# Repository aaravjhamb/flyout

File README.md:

# flyout

a pcb hackercard that also functions as a drone ;D

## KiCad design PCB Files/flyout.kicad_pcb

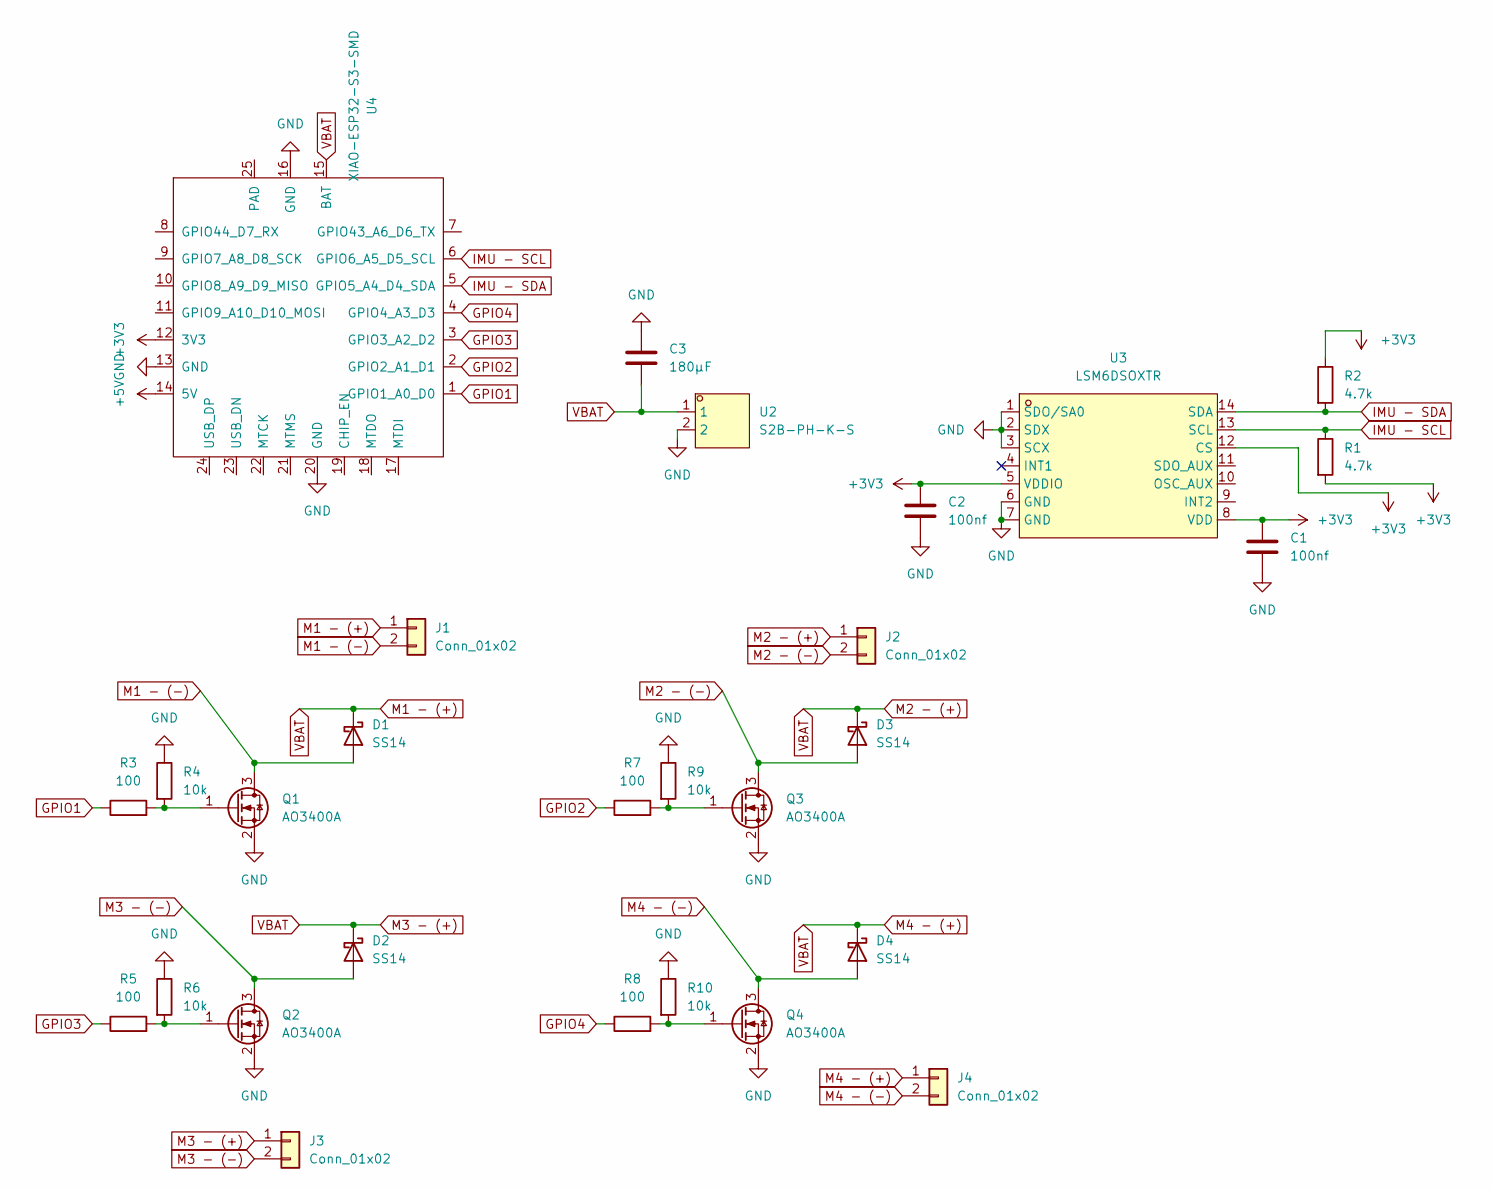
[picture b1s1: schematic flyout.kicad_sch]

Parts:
C1, C2: 100nf; C_0402_1005Metric
C3: 180µF; C_0402_1005Metric
D1, D2, D3, D4: SS14; D_SMA
J1, J2, J3, J4: Conn_01x02; SolderPad_1x02_SMD_1.5x2mm_P2.5mm
Q1, Q2, Q3, Q4: AO3400A; SOT-23
R1, R2: 4.7k; R_0402_1005Metric
R3, R5, R7, R8: 100; R_0402_1005Metric
R4, R6, R9, R10: 10k; R_0402_1005Metric
U2: S2B-PH-K-S; CONN-TH_S2B-PH-K-S-LF-SN; MPN S2B-PH-K-S(LF)(SN); LCSC Part C173752
U3: LSM6DSOXTR; LGA-14L_L3.0-W2.5-P0.50-TL; MPN LSM6DSOXTR; LCSC Part C481766
U4: XIAO-ESP32-S3-SMD

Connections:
+3V3: C1.1, C2.1, R1.2, R2.1, U3.5 (VDDIO), U3.8 (VDD), U3.12 (CS), U4.12 (3V3)
+5V: U4.14 (5V)
GND: C1.2, C2.2, C3.1, Q1.2 (S), Q2.2 (S), Q3.2 (S), Q4.2 (S), R4.1, R6.1, R9.1, R10.1, U2.2, U3.1 (SDO/SA0), U3.2 (SDX), U3.3 (SCX), U3.6 (GND), U3.7 (GND), U4.13 (GND), U4.16 (GND), U4.20 (GND)
GPIO1: R3.1, U4.1 (GPIO1_A0_D0)
GPIO2: R7.1, U4.2 (GPIO2_A1_D1)
GPIO3: R5.1, U4.3 (GPIO3_A2_D2)
GPIO4: R8.1, U4.4 (GPIO4_A3_D3)
IMU - SCL: R1.1, U3.13 (SCL), U4.6 (GPIO6_A5_D5_SCL)
IMU - SDA: R2.2, U3.14 (SDA), U4.5 (GPIO5_A4_D4_SDA)
M1 - (+): C3.2, D1.1 (K), D2.1 (K), D3.1 (K), D4.1 (K), J1.1, J2.1, J3.1, J4.1, U2.1, U4.15 (BAT)
M1 - (-): D1.2 (A), J1.2, Q1.3 (D)
M2 - (-): D3.2 (A), J2.2, Q3.3 (D)
M3 - (-): D2.2 (A), J3.2, Q2.3 (D)
M4 - (-): D4.2 (A), J4.2, Q4.3 (D)
unnamed: Q1.1 (G), R3.2, R4.2
unnamed: Q2.1 (G), R5.2, R6.2
unnamed: Q3.1 (G), R7.2, R9.2
unnamed: Q4.1 (G), R8.2, R10.2

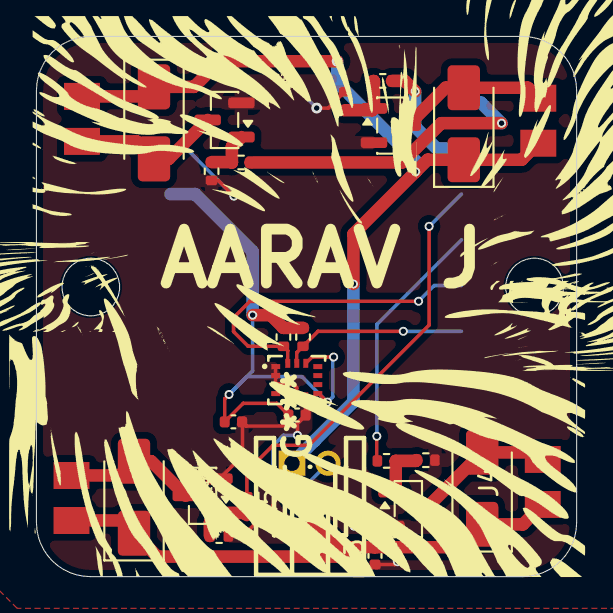
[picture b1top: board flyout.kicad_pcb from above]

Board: 2 copper layers, 30.0 x 30.0 mm, 28 parts (1 on the bottom side), 17 nets.
